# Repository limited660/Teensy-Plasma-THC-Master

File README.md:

# Teensy Plasma THC Master

Loop
- Teensy 3.1
  - CPU Speed : 96MHz
  - Optimize : Fastest with LTO
  - Loop Time : 5.5 microsecond average
  - Cost : $19.80 (7/15/2018)
- Teensy LC
  - CPU Speed : 48MHz
  - Optimize : Faster with LTO
  - Loop Time : 15.7 microsecond average
  - Cost : $11.65 (7/15/2018)

Screen
- RepRap Smart Controller (4x20 with Push Button Encoder)

Button
- One Press = Swap between Tip Target/Hysteresis & save value if changed
- Double Press = Recalls highlighted value from EEPROM
- Hold(Editing Value) = Saves highlighted value to EEPROM, this value is restored on power up and using Double Press
- Hold(Not Editing Value) = Disables output and voltage comparisions, still prints current tip voltage to screen (tip voltage is always printed with small delay) 

Encoder
- Change highlighted value

Frequency Counter
- THCAD should be set to F/1
- Gate interval of 10 milliseconds
- Change mapfloat in Loop to match numbers provided on THCAD

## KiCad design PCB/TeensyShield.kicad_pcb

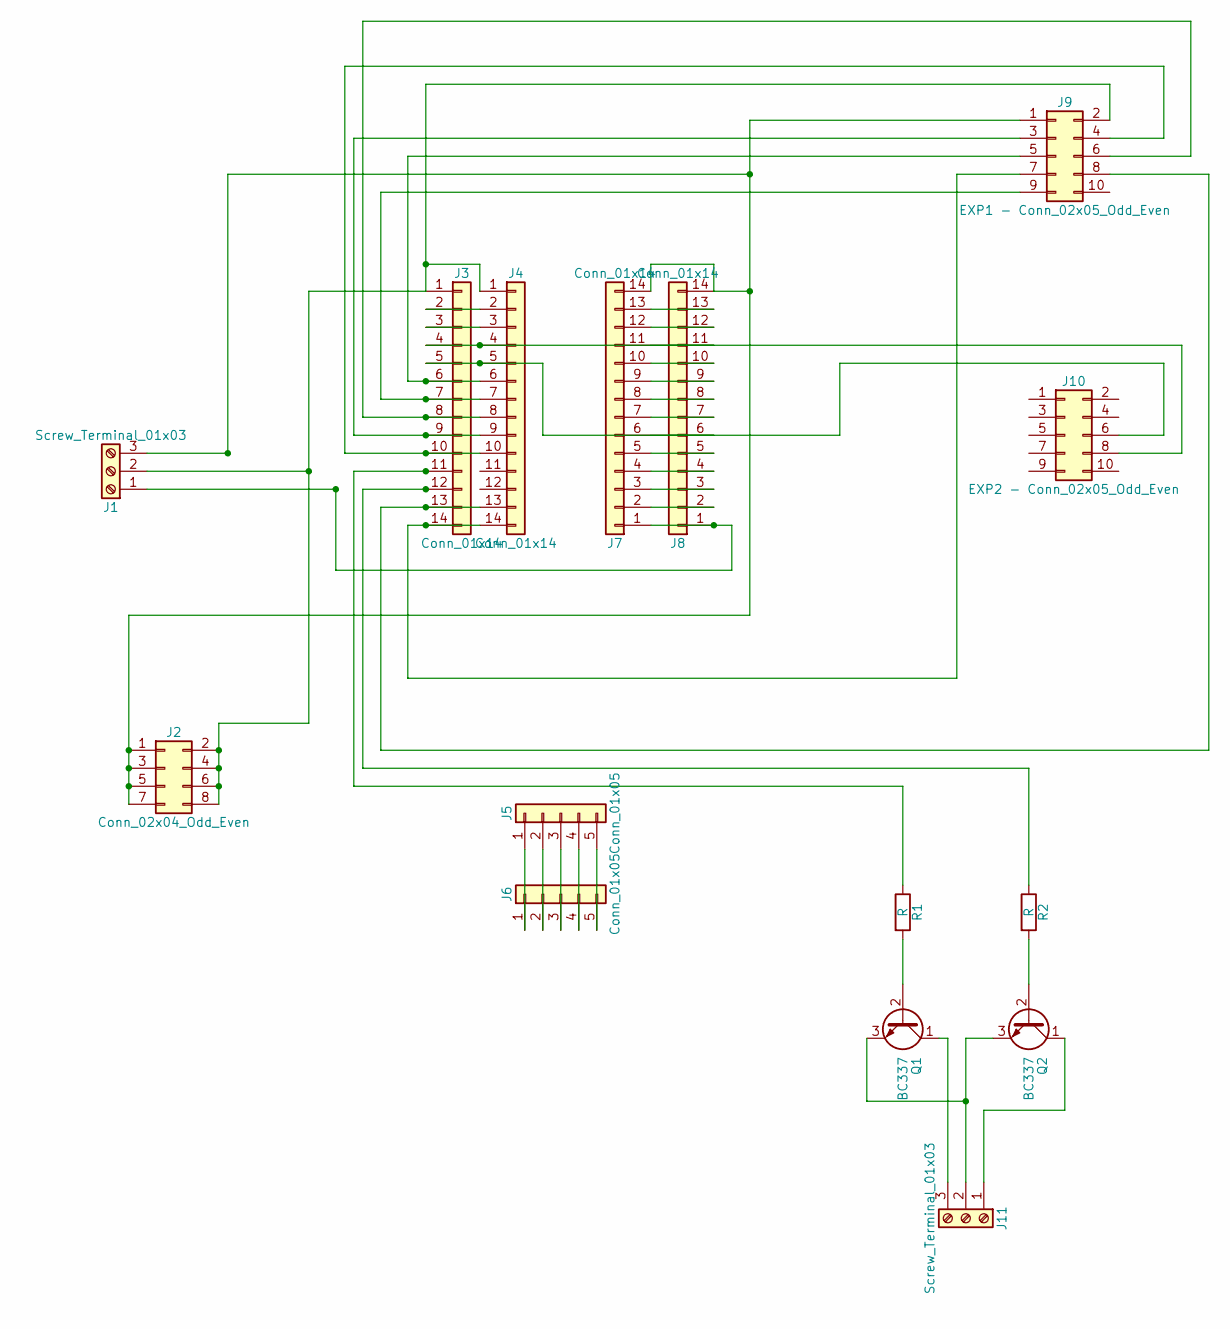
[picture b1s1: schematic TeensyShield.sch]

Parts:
J1, J11: Screw_Terminal_01x03; TerminalBlock_Phoenix_MPT-2.54mm_3pol
J2: Conn_02x04_Odd_Even; Pin_Header_Angled_2x04_Pitch2.54mm
J3, J4, J7, J8: Conn_01x14; Pin_Header_Straight_1x14_Pitch2.54mm
J5, J6: Conn_01x05; Pin_Header_Straight_1x05_Pitch2.54mm
J9: EXP1 - Conn_02x05_Odd_Even; Pin_Header_Straight_2x05_Pitch2.54mm
J10: EXP2 - Conn_02x05_Odd_Even; Pin_Header_Straight_2x05_Pitch2.54mm
Q1, Q2: BC337; TO-92_Molded_Narrow
R1, R2: R; R_Axial_DIN0207_L6.3mm_D2.5mm_P10.16mm_Horizontal

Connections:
unnamed: J1.1, J7.1, J8.1
unnamed: J1.2, J2.2, J2.4, J2.6, J2.8, J3.1, J4.1, J9.2
unnamed: J1.3, J2.1, J2.3, J2.5, J2.7, J7.14, J8.14, J9.1
unnamed: J3.2, J4.2
unnamed: J3.3, J4.3
unnamed: J3.6, J4.6, J9.5
unnamed: J3.7, J4.7, J9.9
unnamed: J3.8, J4.8, J9.6
unnamed: J3.9, J4.9, J9.3
unnamed: J3.10, J4.10, J9.4
unnamed: J3.11, R1.1
unnamed: J3.12, R2.1
unnamed: J3.13, J4.13, J9.8
unnamed: J3.14, J4.14, J9.7
unnamed: J5.1, J6.1
unnamed: J5.2, J6.2
unnamed: J5.3, J6.3
unnamed: J5.4, J6.4
unnamed: J5.5, J6.5
unnamed: J7.2, J8.2
unnamed: J7.3, J8.3
unnamed: J7.4, J8.4
unnamed: J7.5, J8.5
unnamed: J7.6, J8.6
unnamed: J7.7, J8.7
unnamed: J7.8, J8.8
unnamed: J7.9, J8.9
unnamed: J7.10, J8.10
unnamed: J7.11, J8.11
unnamed: J7.12, J8.12
unnamed: J7.13, J8.13
unnamed: J3.5, J4.5, J10.6
unnamed: J3.4, J4.4, J10.8
unnamed: J11.1, Q2.1 (C)
unnamed: J11.2, Q1.3 (E), Q2.3 (E)
unnamed: J11.3, Q1.1 (C)
unnamed: Q1.2 (B), R1.2
unnamed: Q2.2 (B), R2.2

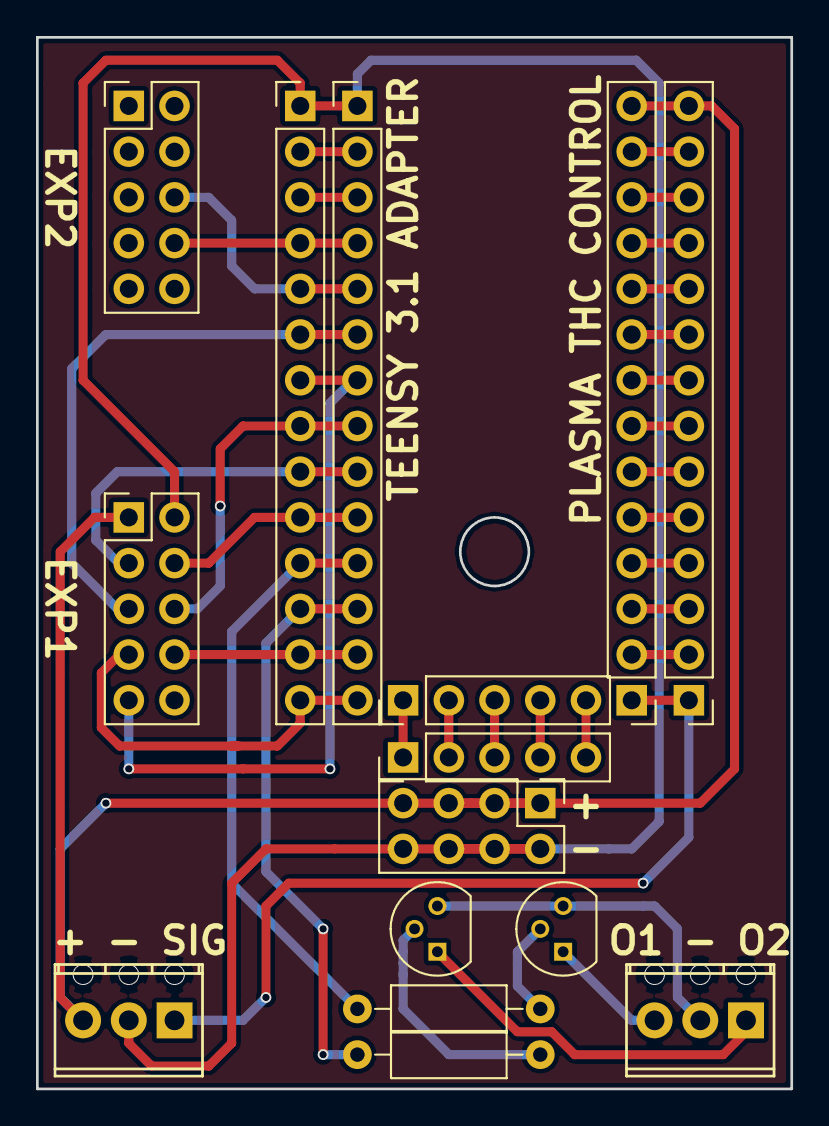
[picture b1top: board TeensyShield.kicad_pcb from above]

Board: 2 copper layers, 41.9 x 58.4 mm, 15 parts (0 on the bottom side), 38 nets.

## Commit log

2018-07-04 Initial upload
2018-07-04 Name change
2018-07-04 Small change
2018-07-05 Branch Test
2018-07-05 Removed unnecessary code
2018-07-05 Added LCD print skips if value matches previous
    Will not print to LCD if output status matches previous or if torch value matches previous. Torch value is still continuously monitored and outputs are not affected by LCD checks.
2018-07-06 Change PrevTorch to float
    Direct comparison so small changes can be seen on LCD, minimal speed difference. Loop now runs at 7-11 microseconds.
2018-07-12 Testing of code successful, loop time down to 7-12 microseconds on Teensy 3.1 (#1)
    Testing of code successful, loop time down to 7-12 microseconds on Teensy 3.1
2018-07-14 Min/Max Volt Changes, Cleanup
    - Added minVolt and maxVolt variables
    - Extended working range of output to prevent head crashes
    - Removed unused variables
    - Removed all serial and code timing
    - Added library link for FreqCount
    - Added message for over voltage to signify output is off
2018-07-15 Added button function to disable outputs
    Added function to button hold to disable outputs if ButtonPress is not 1 or 2 (not editing a value), it will print "DISABLED" on Tip Target and Hysteresis, turn outputs off, and write status to EEPRO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
2018-07-16 Fixed LCD blanking when using save
    Fixed a problem where screen would not clear "SAVED" text after saving a value, changing the value using the encoder, and then applying that value.
2018-07-16 KICAD PCB Files
2018-07-16 Moved output toggling before if statement
    Moved toggling to prevent extra cycles if output already switched
